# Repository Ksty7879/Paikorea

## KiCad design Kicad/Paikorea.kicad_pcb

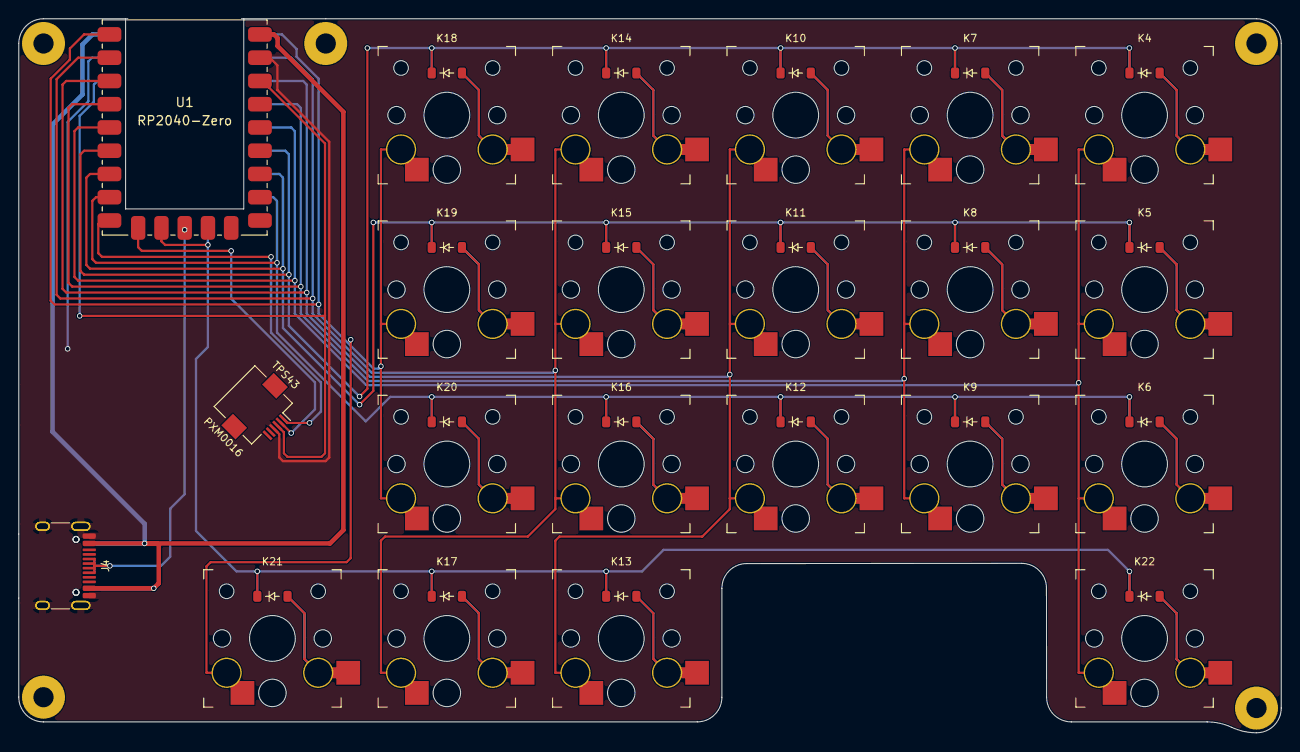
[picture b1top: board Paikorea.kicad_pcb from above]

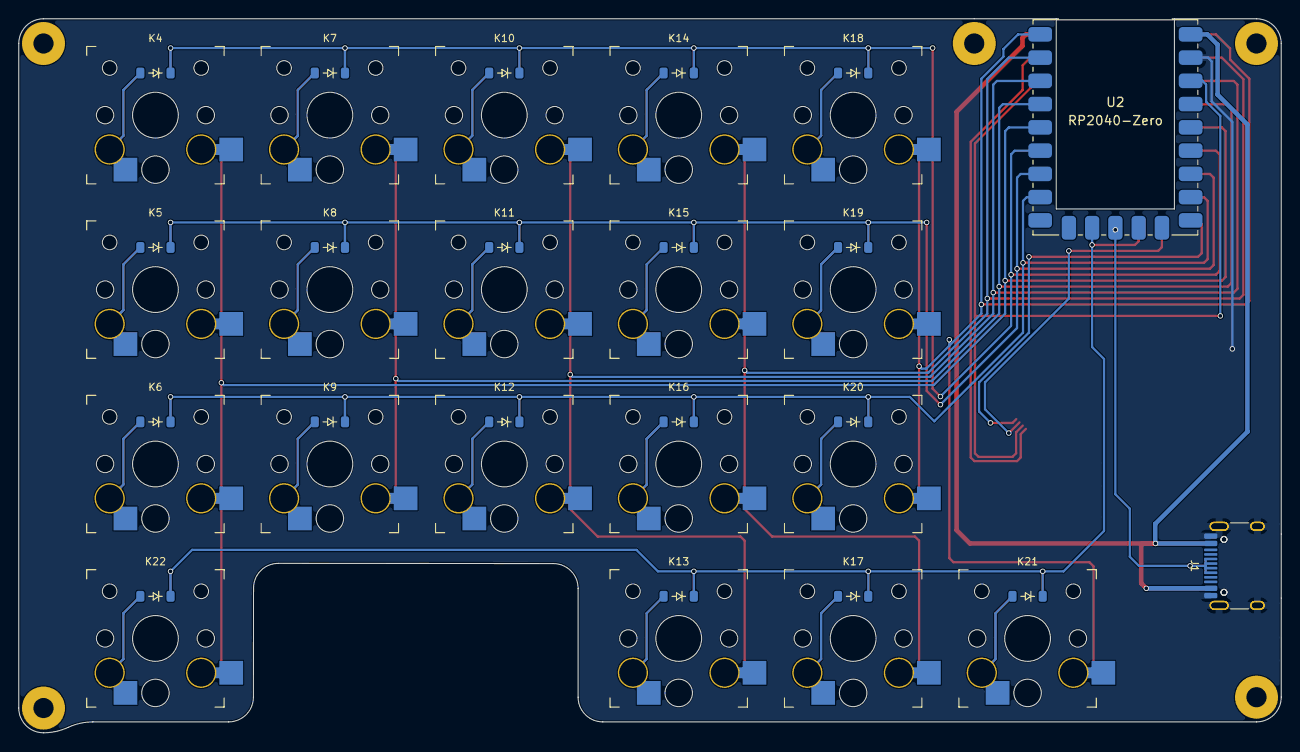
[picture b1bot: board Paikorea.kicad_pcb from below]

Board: 2 copper layers, 137.9 x 78.0 mm, 49 parts (2 on the bottom side), 34 nets.

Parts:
D4, D5, D6, D7, D8, D9, D10, D11, D12, D13, D14, D15, D16, D17, D18, D19, D20, D21, D22: 1N4148_SMD; D_SOD-123_dual
J1, J4: USB-C link; USB_C_Receptacle_HRO_TYPE-C-31-M-12
J2: TPS43-201A-S; Hirose_FH12-6S-0.5SH_1x06-1MP_P0.50mm_Horizontal
K4, K5, K6, K7, K8, K9, K10, K11, K12, K13, K14, K15, K16, K17, K18, K19, K20, K21, K22: Choc_v1v2; SW_Choc_v1v2_HS_Reversible
N1, N2, N5, N6, N7: 4.2mm; MAC8_TH0816-XX-M2-NPTHhole
TRK1: TPS43-201A-S; Azoteq_TPS43_201A_S
U1, U2: RP2040-Zero; RP2040-Zero-smd

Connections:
+3V3: J2.3, U1.21 (3V3), U2.21 (3V3)
+5V: J1.A4, J1.A9, J1.B4, J1.B9, J4.A4, J4.A9, J4.B4, J4.B9, U1.23 (5V), U2.23 (5V)
Data: J1.A6, J1.A7, J1.B6, J1.B7, J4.A6, J4.A7, J4.B6, J4.B7, U1.12 (GP11), U2.12 (GP11)
GND: J1.A1, J1.A12, J1.B1, J1.B12, J1.SH, J2.4, J4.A1, J4.A12, J4.B1, J4.B12, J4.SH, U1.22 (GND), U2.22 (GND)
unnamed: D4.2, K4.2
unnamed: D5.2, K5.2
unnamed: D6.2, K6.2
unnamed: D7.2, K7.2
unnamed: D8.2, K8.2
unnamed: D9.2, K9.2
unnamed: D10.2, K10.2
unnamed: D11.2, K11.2
unnamed: D12.2, K12.2
unnamed: D13.2, K13.2
unnamed: D14.2, K14.2
unnamed: D15.2, K15.2
unnamed: D16.2, K16.2
unnamed: D17.2, K17.2
unnamed: D18.2, K18.2
unnamed: D19.2, K19.2
unnamed: D20.2, K20.2
unnamed: D21.2, K21.2
unnamed: D22.2, K22.2
SCL: J2.2, U1.10 (GP9)
SDA: J2.1, U1.9 (GP8)
col1: K4.1, K5.1, K6.1, K22.1, U1.5 (GP4), U2.5 (GP4)
col2: K7.1, K8.1, K9.1, U1.4 (GP3), U2.4 (GP3)
col3: K10.1, K11.1, K12.1, K13.1, U1.3 (GP2), U2.3 (GP2)
col4: K14.1, K15.1, K16.1, K17.1, U1.2 (GP1), U2.2 (GP1)
col5: K18.1, K19.1, K20.1, K21.1, U1.1 (GP0), U2.1 (GP0)
row0: D4.1, D7.1, D10.1, D14.1, D18.1, U1.6 (GP5), U2.6 (GP5)
row1: D5.1, D8.1, D11.1, D15.1, D19.1, U1.7 (GP6), U2.7 (GP6)
row2: D6.1, D9.1, D12.1, D16.1, D20.1, U1.8 (GP7), U2.8 (GP7)
row3: D13.1, D17.1, D21.1, D22.1, U1.11 (GP10), U2.11 (GP10)

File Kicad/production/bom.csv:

Designator,Footprint,Quantity,Value,LCSC Part #
"D10, D11, D12, D13, D14, D15, D16, D17, D18, D19, D20, D21, D22, D4, D5, D6, D7, D8, D9",D_SOD-123_dual,19,1N4148_SMD,
"J1, J4",AUDIO-SMD_PJ-320D-1,2,AudioJack3,C431535
J2,Hirose_FH12-6S-0.5SH_1x06-1MP_P0.50mm_Horizontal,1,TPS43-201A-S,
"K10, K11, K12, K13, K14, K15, K16, K17, K18, K19, K20, K21, K22, K4, K5, K6, K7, K8, K9",SW_Kailh_PG1316S_1.00u_Dual2,19,PG1316S,
"N1, N2, N5, N6, N7",MAC8_TH0816-XX-M2-NPTHhole,5,4.2mm,
TRK1,Azoteq_TPS43_201A_S,1,TPS43-201A-S,
"U1, U2",RP2040-Zero-smd,2,RP2040-Zero,
